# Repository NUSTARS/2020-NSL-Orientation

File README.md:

# bno_stars
The best sub-sub team

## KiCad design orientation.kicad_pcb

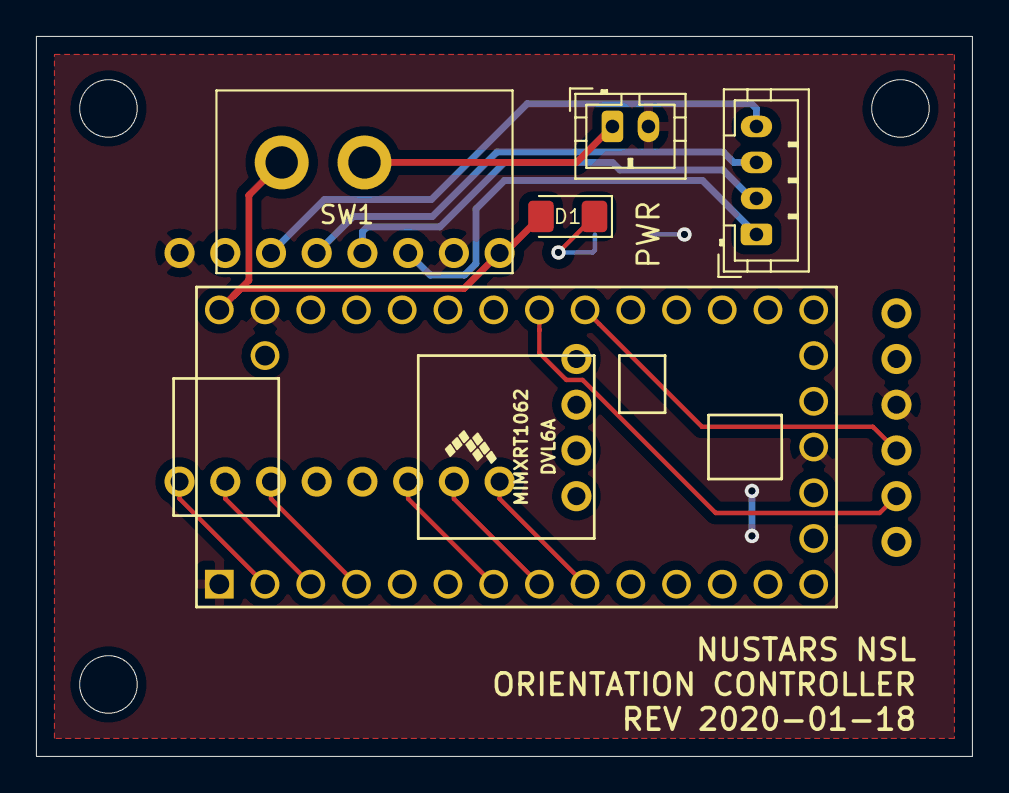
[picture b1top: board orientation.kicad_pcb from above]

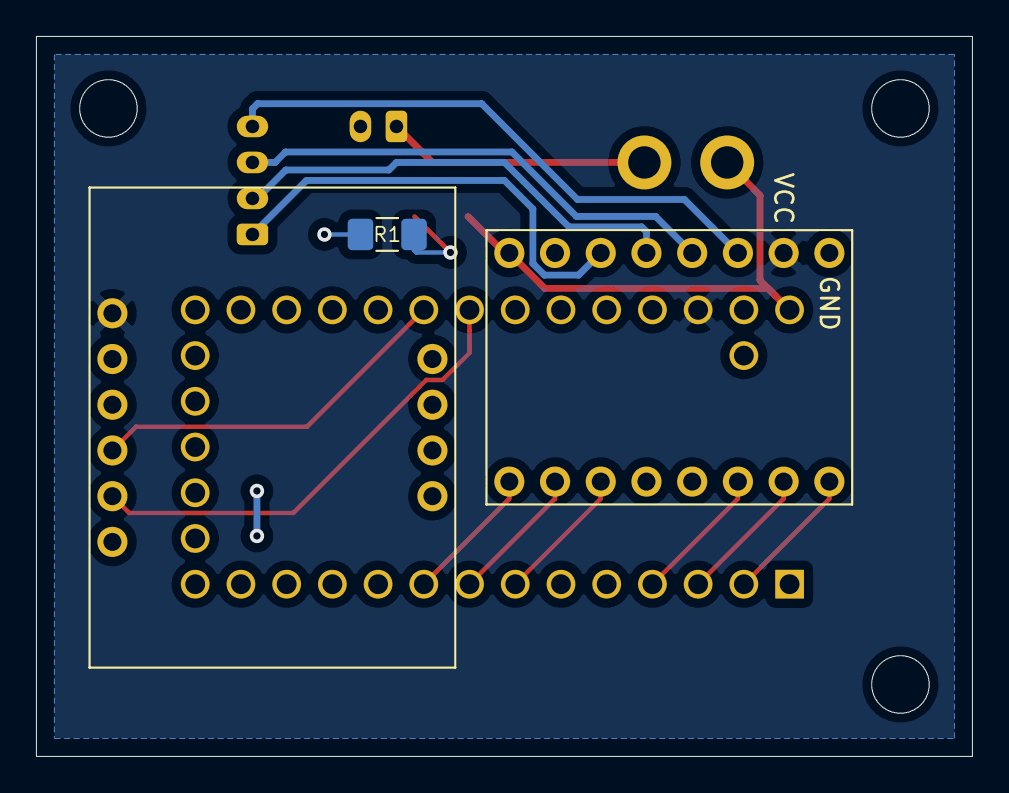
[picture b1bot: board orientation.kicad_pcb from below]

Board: 2 copper layers, 52.0 x 40.0 mm, 8 parts (3 on the bottom side), 17 nets.

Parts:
D1: LED; LED_1206_3216Metric_Pad1.42x1.75mm_HandSolder
J1: Conn_01x02; JST_PH_B2B-PH-K_1x02_P2.00mm_Vertical
J2: Conn_01x04; JST_PH_B4B-PH-K_1x04_P2.00mm_Vertical
R1: 110; R_1206_3216Metric_Pad1.42x1.75mm_HandSolder
SW1: SW_SPST; GF-123-0054
U1: Teensy4.0; Teensy40
U2: STSPIN220
U3: bno055

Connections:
3V3T: U1.31, U2.10, U3.1
GND: J1.2, R1.2, U1.1, U1.17, U1.32, U2.9, U2.15, U3.3
unnamed: D1.1, R1.1
unnamed: J1.1, SW1.1
unnamed: J2.1, U2.14
unnamed: J2.2, U2.13
unnamed: J2.3, U2.12
unnamed: J2.4, U2.11
unnamed: U1.2, U2.8
unnamed: U1.3, U2.7
unnamed: U1.4, U2.6
unnamed: U1.7, U2.3
unnamed: U1.8, U2.2
unnamed: U1.9, U2.1
SCL: U1.26, U3.5
SDA: U1.25, U3.4
VBAT: D1.2, SW1.2, U1.33, U2.16

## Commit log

2020-02-19 moving day
2020-02-20 Copy
2020-02-20 no copy
2020-03-06 updated our child imogen
2020-03-08 demonstration
